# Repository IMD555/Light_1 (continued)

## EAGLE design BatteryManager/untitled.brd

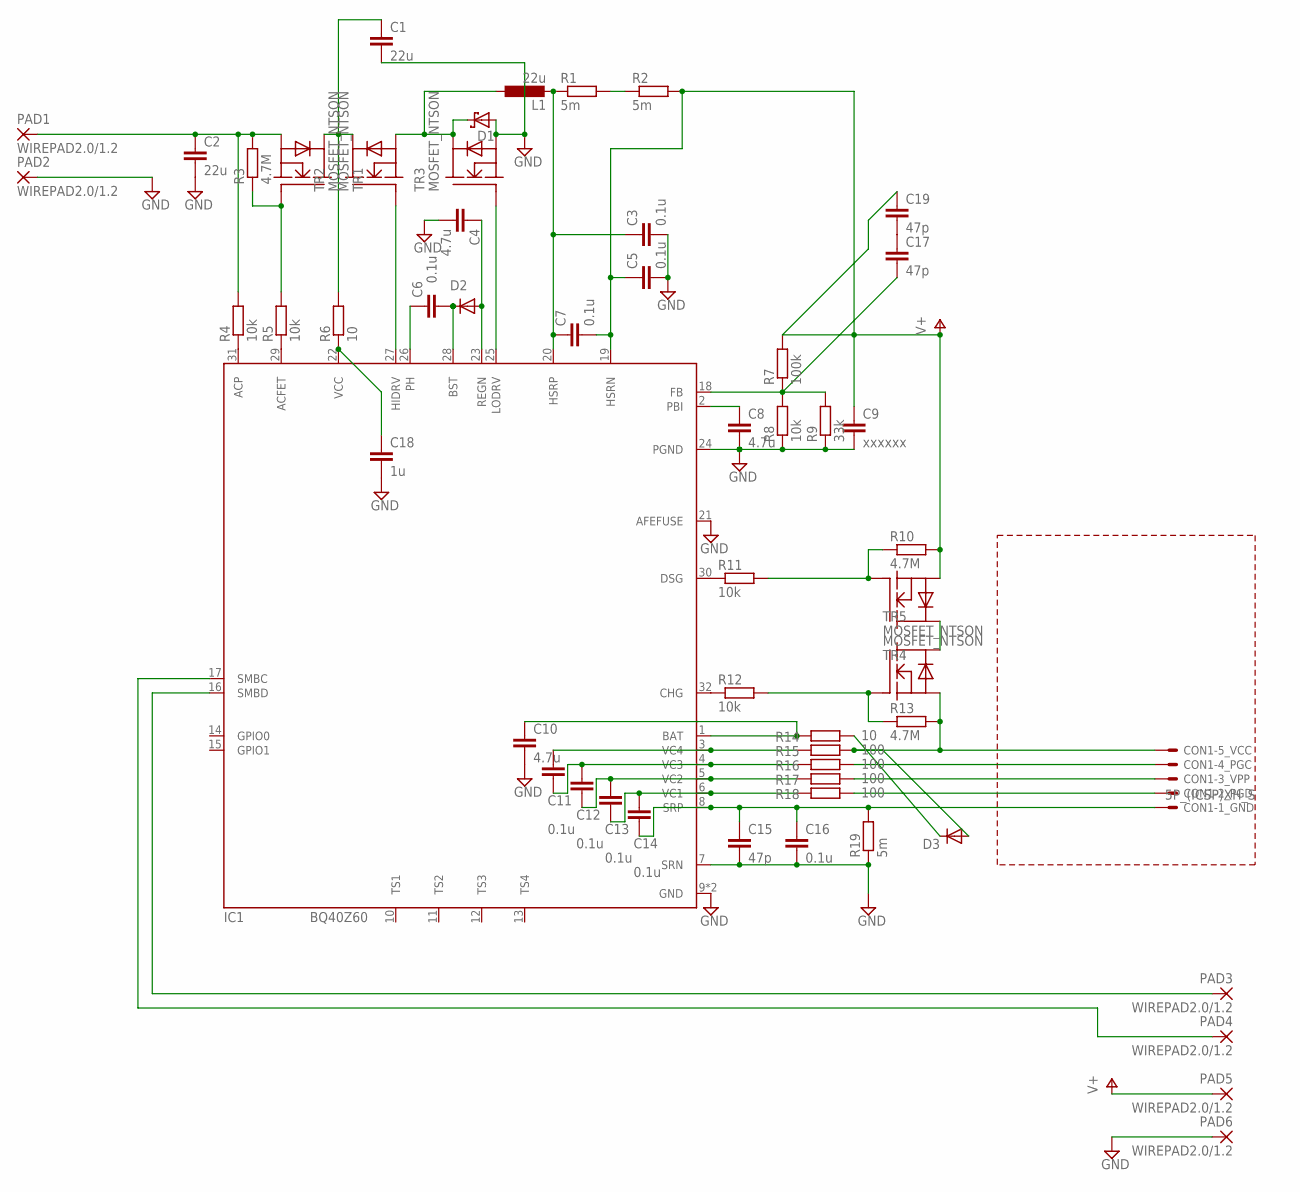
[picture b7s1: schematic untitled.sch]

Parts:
C1, C2: 22u; C1210
C3, C5, C6, C7, C11, C12, C13, C14, C16: 0.1u; C0402
C4: 4.7u; C0402
C8, C10: 4.7u; C0805
C9: xxxxxx; C0402
C15, C17, C19: 47p; C0402
C18: 1u; C0402
CON1: 5P_(ICSP)XH_S; XH-5_S
D1: SCHOTTKY-DIODETO-277A; TO-277A
D2, D3: DIODE-VMN2; VMN2
IC1: BQ40Z60; QFN32
L1: 22u; SCRH125
PAD1, PAD2, PAD3, PAD4, PAD5, PAD6: WIREPAD2.0/1.2; 2.0/1.3
R1, R2, R19: 5m; R1210
R3, R10, R13: 4.7M; R0402
R4, R5, R8, R11, R12: 10k; R0402
R6, R14: 10; R0402
R7: 100k; R0402
R9: 33k; R0402
R15, R16, R17, R18: 100; R0402
TR1, TR2, TR3, TR4, TR5: MOSFET_NTSON; TSON_ADVANCE

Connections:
GND: C1.2, C2.2, C3.2, C4.2, C5.2, C8.2, C9.2, C10.2, C15.2, C16.2, C18.2, D1.A, IC1.7 (SRN), IC1.9 (GND), IC1.21 (AFEFUSE), IC1.24 (PGND), IC1.EXP (GND), PAD2.1, PAD6.1, R8.1, R9.1, R19.1, TR3.1 (S), TR3.2 (S), TR3.3 (S)
unnamed: CON1.4, R18.2
unnamed: R1.2, R2.1
unnamed: D3.C, R14.2
unnamed: CON1.3, R17.2
unnamed: C17.1, C19.2
unnamed: CON1.2, R16.2
unnamed: CON1.1, D3.A, R13.2, R15.2, TR5.1 (S), TR5.2 (S), TR5.3 (S)
unnamed: TR4.5 (D), TR4.6 (D), TR4.7 (D), TR4.8 (D), TR4.DRAIN1 (D), TR4.DRAIN2 (D), TR5.5 (D), TR5.6 (D), TR5.7 (D), TR5.8 (D), TR5.DRAIN1 (D), TR5.DRAIN2 (D)
unnamed: C14.2, C15.1, C16.1, CON1.5, IC1.8 (SRP), R19.2
unnamed: C10.1, IC1.1 (BAT), R14.1
unnamed: IC1.30 (DSG), R11.1
unnamed: IC1.32 (CHG), R12.1
unnamed: R12.2, R13.1, TR5.4 (G)
unnamed: R10.1, R11.2, TR4.4 (G)
unnamed: C8.1, IC1.2 (PBI)
unnamed: C11.2, C12.1, IC1.4 (VC3), R16.1
unnamed: C17.2, IC1.18 (FB), R7.1, R8.2, R9.2
unnamed: C12.2, C13.1, IC1.5 (VC2), R17.1
unnamed: IC1.29 (ACFET), R5.1
unnamed: R3.1, R5.2, TR1.4 (G)
unnamed: C6.1, IC1.26 (PH)
unnamed: C6.2, D2.C, IC1.28 (BST)
unnamed: C4.1, D2.A, IC1.23 (REGN)
unnamed: D1.C, L1.1, TR2.1 (S), TR2.2 (S), TR2.3 (S), TR3.5 (D), TR3.6 (D), TR3.7 (D), TR3.8 (D), TR3.DRAIN1 (D), TR3.DRAIN2 (D)
unnamed: C1.1, R6.2, TR1.5 (D), TR1.6 (D), TR1.7 (D), TR1.8 (D), TR1.DRAIN1 (D), TR1.DRAIN2 (D), TR2.5 (D), TR2.6 (D), TR2.7 (D), TR2.8 (D), TR2.DRAIN1 (D), TR2.DRAIN2 (D)
unnamed: IC1.27 (HIDRV), TR2.4 (G)
unnamed: IC1.25 (LODRV), TR3.4 (G)
unnamed: C3.1, C7.1, IC1.20 (HSRP), L1.2, R1.1
unnamed: IC1.31 (ACP), R4.1
unnamed: C2.1, PAD1.1, R3.2, R4.2, TR1.1 (S), TR1.2 (S), TR1.3 (S)
unnamed: C18.1, IC1.22 (VCC), R6.1
unnamed: C13.2, C14.1, IC1.6 (VC1), R18.1
unnamed: C11.1, IC1.3 (VC4), R15.1
unnamed: IC1.17 (SMBC), PAD4.1
unnamed: IC1.16 (SMBD), PAD3.1
V+: C5.1, C7.2, C9.1, C19.1, IC1.19 (HSRN), PAD5.1, R2.2, R7.2, R10.2, TR4.1 (S), TR4.2 (S), TR4.3 (S)

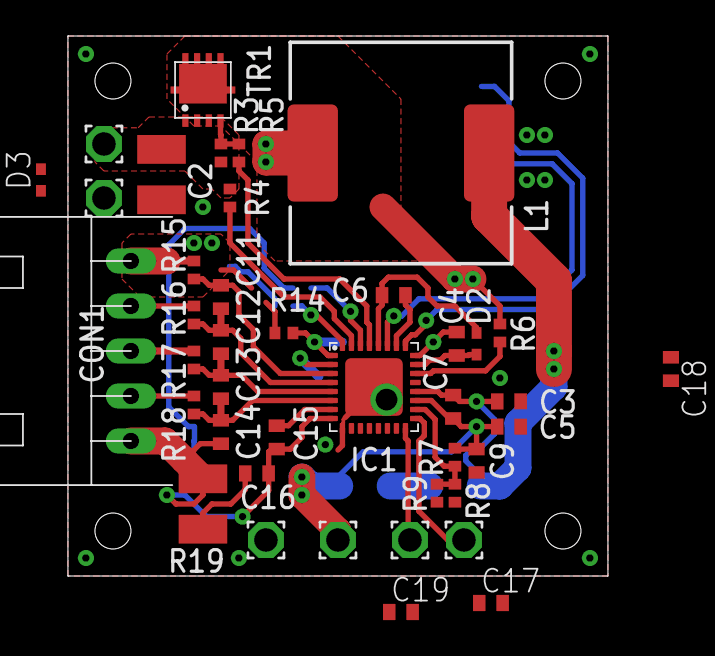
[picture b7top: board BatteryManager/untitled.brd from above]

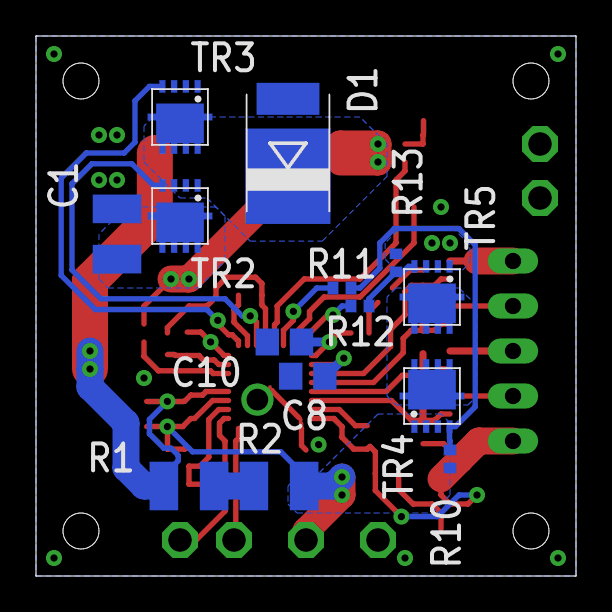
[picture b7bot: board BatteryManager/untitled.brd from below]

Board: 2 copper layers, 30.0 x 30.0 mm, 55 parts (14 on the bottom side), 37 nets.

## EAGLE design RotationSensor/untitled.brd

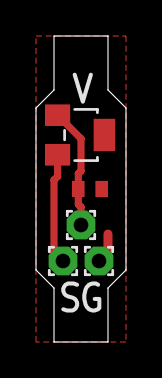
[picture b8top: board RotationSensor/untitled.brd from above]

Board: 2 copper layers, 5.0 x 17.0 mm, 7 parts (0 on the bottom side), 3 nets.

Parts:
C1: C0402
IC7: SI7201-B-00-FV; SOT23-W
PAD19, PAD20, PAD21: WIREPAD1,6/0,8; 1,6/0,8
U$1, U$4: RULER-S

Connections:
GND1: C1.2, IC7.3, PAD21.1
unnamed: IC7.2, PAD19.1
VDD1: C1.1, IC7.1, PAD20.1

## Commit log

2021-03-15 first
2021-03-15 rearrange directry tree
2021-03-17 add vscode support
2021-03-17 cleand and added .gitignore
